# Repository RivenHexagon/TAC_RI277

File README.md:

# Total Audio Concepts (TAC) Scorpion Mixing Console Overhaul
## PCB RI277

Redesign of the Input Connector Card (PCB RI277) in order to populate it
with gold plated Audio Jacks. I made 6 of them fit a copper plated Eurocard
(100 mm x 80 mm) substrate for DIY etching.

## Made With

I named the new version RI277D and made them with KiCad 5.1.7. using a git
submodule that handles any special footprints:

https://github.com/RivenHexagon/TAC_KiCad_lib.git

## Further Modifications

The XLR Bus Out connectors were panel mounted and solder wired to the PCB as
well as the Tape Return wiring harness. I've provided two 3-pin Molex connectors
instead.

Mirrored image of the original PCB:

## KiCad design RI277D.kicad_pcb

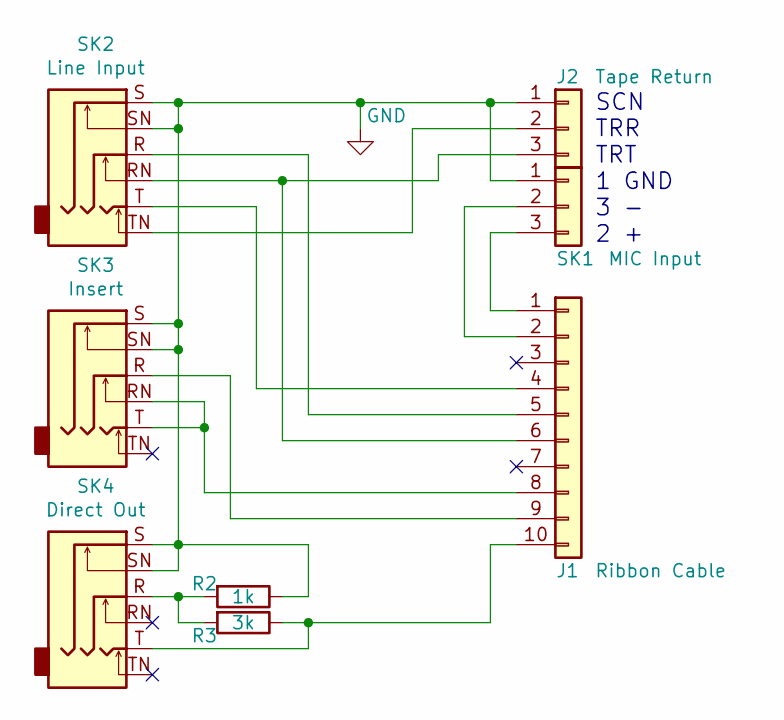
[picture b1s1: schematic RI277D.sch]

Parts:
J1: Ribbon Cable; Molex_KK-254_AE-6410-10A_1x10_P2.54mm_Vertical
J2: Tape Return; Molex_KK-254_AE-6410-03A_1x03_P2.54mm_Vertical
R2: 1k; R_Axial_DIN0207_L6.3mm_D2.5mm_P10.16mm_Horizontal
R3: 3k; R_Axial_DIN0207_L6.3mm_D2.5mm_P10.16mm_Horizontal
SK1: MIC Input; Molex_KK-254_AE-6410-03A_1x03_P2.54mm_Vertical
SK2: Line Input; CL13345
SK3: Insert; CL13345
SK4: Direct Out; CL13345

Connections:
GND: J2.1, R2.1, SK1.1, SK2.S, SK2.SN, SK3.S, SK3.SN, SK4.S, SK4.SN
unnamed: J1.1, SK1.3
unnamed: J1.2, SK1.2
unnamed: J1.4, SK2.T
unnamed: J1.5, SK2.R
unnamed: J1.6, J2.3, SK2.RN
unnamed: J1.8, SK3.RN, SK3.T
unnamed: J1.9, SK3.R
unnamed: J1.10, R3.1, SK4.T
unnamed: J2.2, SK2.TN
unnamed: R2.2, R3.2, SK4.R

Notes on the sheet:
SCN TRR TRT 1 GND 3 - 2 +

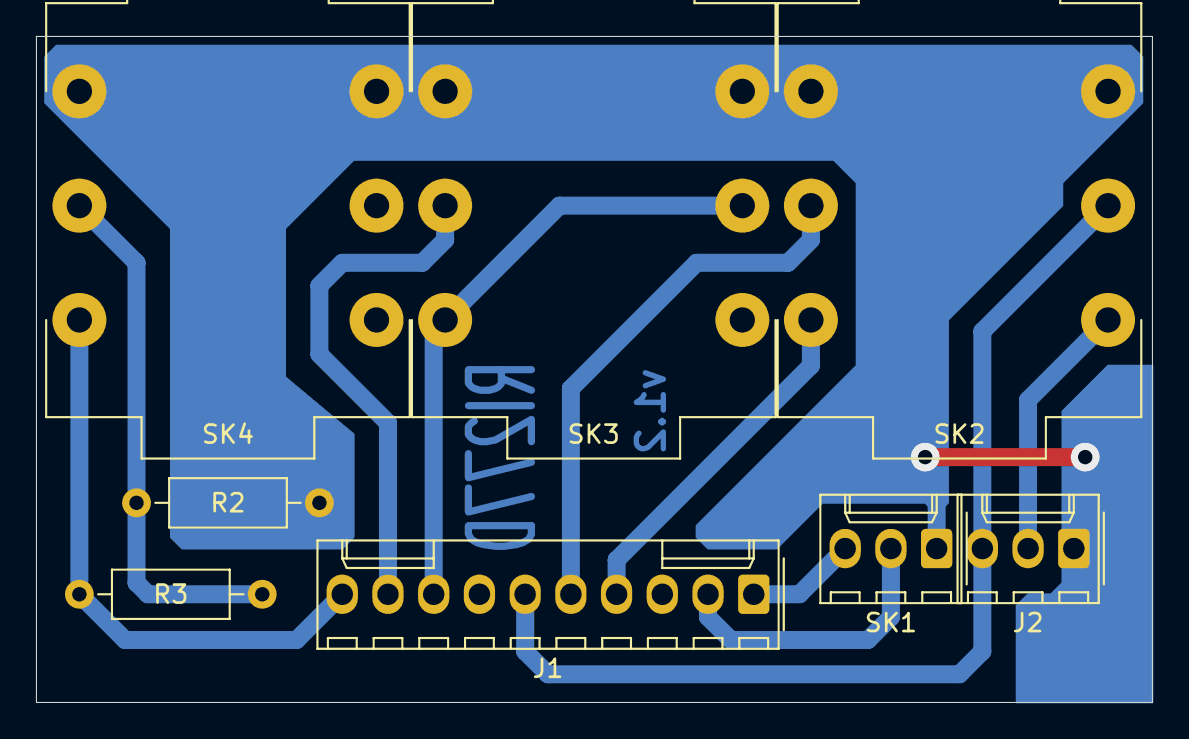
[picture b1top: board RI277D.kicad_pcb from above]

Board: 2 copper layers, 62.0 x 37.0 mm, 8 parts (0 on the bottom side), 11 nets.

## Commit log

2020-10-27 version 1.1
2020-10-27 version 1.2 prototype ready
2020-11-30 added git submodule library and wirebridge to layout
2020-11-30 removed old local lib cliff
2020-11-30 added readme and img
